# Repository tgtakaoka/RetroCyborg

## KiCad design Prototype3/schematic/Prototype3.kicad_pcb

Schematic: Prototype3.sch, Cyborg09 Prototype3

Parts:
C1, C2, C3, C4, C5: 0.1u; C_0603_1608Metric
C6, C7, C8, C9: 22p; C_0402_1005Metric
J1: Conn_I2C_Master; PinSocket_1x04_P2.54mm_Vertical
J2: Conn_Micro_SD; PinSocket_1x07_P2.54mm_Vertical
J3: Conn_USB_Serial; PinSocket_1x06_P2.54mm_Vertical
J4, J5: Conn_AVR_ISP; PinSocket_1x06_P2.54mm_Vertical
R1, R2: 4k7; R_0603_1608Metric
R3, R4, R5, R6: 10k; R_0603_1608Metric
U1: ATmega1284P-PU; DIP-40_W15.24mm_Socket
U2: HM628128DLP-5; DIP-32_W15.24mm_Socket
U3: HD63C09E; DIP-40_W15.24mm_Socket
U4: ATmega328-PU; DIP-28_W7.62mm_Socket
Y1, Y2: 20MHz; Crystal_SMD_SeikoEpson_FA238-4Pin_3.2x2.5mm

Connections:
/A0: U1.25 (PC3), U2.26 (A9), U3.8 (A0)
/A1: U1.24 (PC2), U2.25 (A11), U3.9 (A1)
/A2: J5.4 (MISO), U2.23 (A10), U3.10 (A2), U4.18 (MISO/PB4)
/A3: J5.5 (MOSI), U2.3 (A14), U3.11 (A3), U4.17 (MOSI/PB3)
/A4: U2.4 (A12), U3.12 (A4), U4.16 (~SS~/PB2)
/A5: U2.5 (A7), U3.13 (A5), U4.2 (RXD/PD0)
/A6: U2.6 (A6), U3.14 (A6), U4.15 (PB1)
/A7: J5.3 (SCK), U2.7 (A5), U3.15 (A7), U4.19 (SCK/PB5)
/A8: U2.8 (A4), U3.16 (A8), U4.14 (PB0)
/A9: U2.9 (A3), U3.17 (A9), U4.3 (TXD/PD1)
/A10: U2.10 (A2), U3.18 (A10), U4.4 (PD2)
/A11: U2.11 (A1), U3.19 (A11), U4.5 (PD3)
/A12: U2.12 (A0), U3.20 (A12), U4.6 (PD4)
/A13: U2.31 (A15), U3.21 (A13), U4.11 (PD5)
/A14: U2.28 (A13), U3.22 (A14), U4.12 (PD6)
/A15: U2.27 (A8), U3.23 (A15), U4.13 (PD7)
/AVMA: U1.26 (PC4), U3.36 (AVMA)
/BA: U1.27 (PC5), U3.6 (BA)
/BS: U1.29 (PC7), U3.5 (BS)
/CLK_E: U2.30 (CS2), U3.34 (E), U4.27 (SDA/PC4)
/CLK_Q: U3.35 (Q), U4.28 (SCL/PC5)
/D0: U1.40 (PA0), U2.21 (Q7), U3.31 (D0)
/D1: U1.39 (PA1), U2.20 (Q6), U3.30 (D1)
/D2: U1.38 (PA2), U2.19 (Q5), U3.29 (D2)
/D3: U1.37 (PA3), U2.18 (Q4), U3.28 (D3)
/D4: U1.36 (PA4), U2.17 (Q3), U3.27 (D4)
/D5: U1.35 (PA5), U2.13 (Q0), U3.26 (D5)
/D6: U1.34 (PA6), U2.14 (Q1), U3.25 (D6)
/D7: U1.33 (PA7), U2.15 (Q2), U3.24 (D7)
/DBG_RX: J3.3 (TXD), U1.14 (RXD0/PD0)
/DBG_TX: J3.2 (RXD), U1.15 (TXD0/PD1)
/LIC: U1.19 (PD5), U3.38 (LIC)
/RD_WR: U1.4 (PB3), U2.29 (WR), U3.32 (R/~W)
/SCL: J1.4 (SCL), R1.2, U1.22 (SCL/PC0)
/SDA: J1.1 (SDA), R2.2, U1.23 (SDA/PC1)
/SD_CD: J2.6 (CD), U1.16 (RXD1/PD2)
/SD_DI: J2.3 (DI), J4.5 (MOSI), U1.6 (MOSI/PB5)
/SD_DO: J2.5 (DO), J4.4 (MISO), U1.7 (MISO/PB6)
/SD_SCK: J2.4 (SCK), J4.3 (SCK), U1.8 (SCK/PB7)
/~ACK: U1.20 (PD6), U4.25 (PC2)
/~DBG_RST~: C5.2, J4.1 (~RESET~), R3.1, U1.9 (~RESET~)
/~DBG_RTS: J3.5 (~CTS), U1.18 (PD4)
/~HALT: U1.1 (PB0), U3.40 (~HALT)
/~INT: U1.17 (TXD1/PD3), U4.26 (PC3)
/~IRQ: U1.2 (PB1), U3.3 (~IRQ)
/~RAM_E: U1.28 (PC6), U2.22 (CS1)
/~RESET: U1.3 (PB2), U3.37 (~RESET)
/~SD_CS: J2.2 (~CS), U1.5 (~SS~/PB4)
/~STEP: U1.21 (PD7), U4.24 (PC1)
GND: C1.2, C2.2, C3.2, C4.2, C6.2, C7.1, C8.2, C9.1, J1.3 (GND), J2.7 (GND), J3.6 (GND), J4.6 (GND), J5.6 (GND), U1.11 (GND), U1.31 (GND), U2.2 (A16), U2.16 (GND), U2.24 (OE), U3.1 (VSS), U3.39 (TSC), U4.8 (GND), U4.22 (GND)
unnamed: C5.1, J3.1 (~DTR)
unnamed: C6.1, U1.13 (XTAL1), Y1.1
unnamed: C7.2, U1.12 (XTAL2), Y1.2
unnamed: C8.1, U4.9 (XTAL1/PB6), Y2.1
unnamed: C9.2, U4.10 (XTAL2/PB7), Y2.2
unnamed: J5.1 (~RESET~), R6.2, U4.1 (PC6/~RESET)
unnamed: R4.1, U3.2 (~NMI)
unnamed: R5.1, U3.4 (~FIRQ)
VCC: C1.1, C2.1, C3.1, C4.1, J1.2 (5V0), J2.1 (VCC), J3.4 (5V0), J4.2 (VCC), J5.2 (VCC), R1.1, R2.1, R3.2, R4.2, R5.2, R6.1, U1.10 (VCC), U1.30 (AVCC), U2.32 (VCC), U3.7 (VCC), U4.7 (VCC), U4.20 (AVCC)

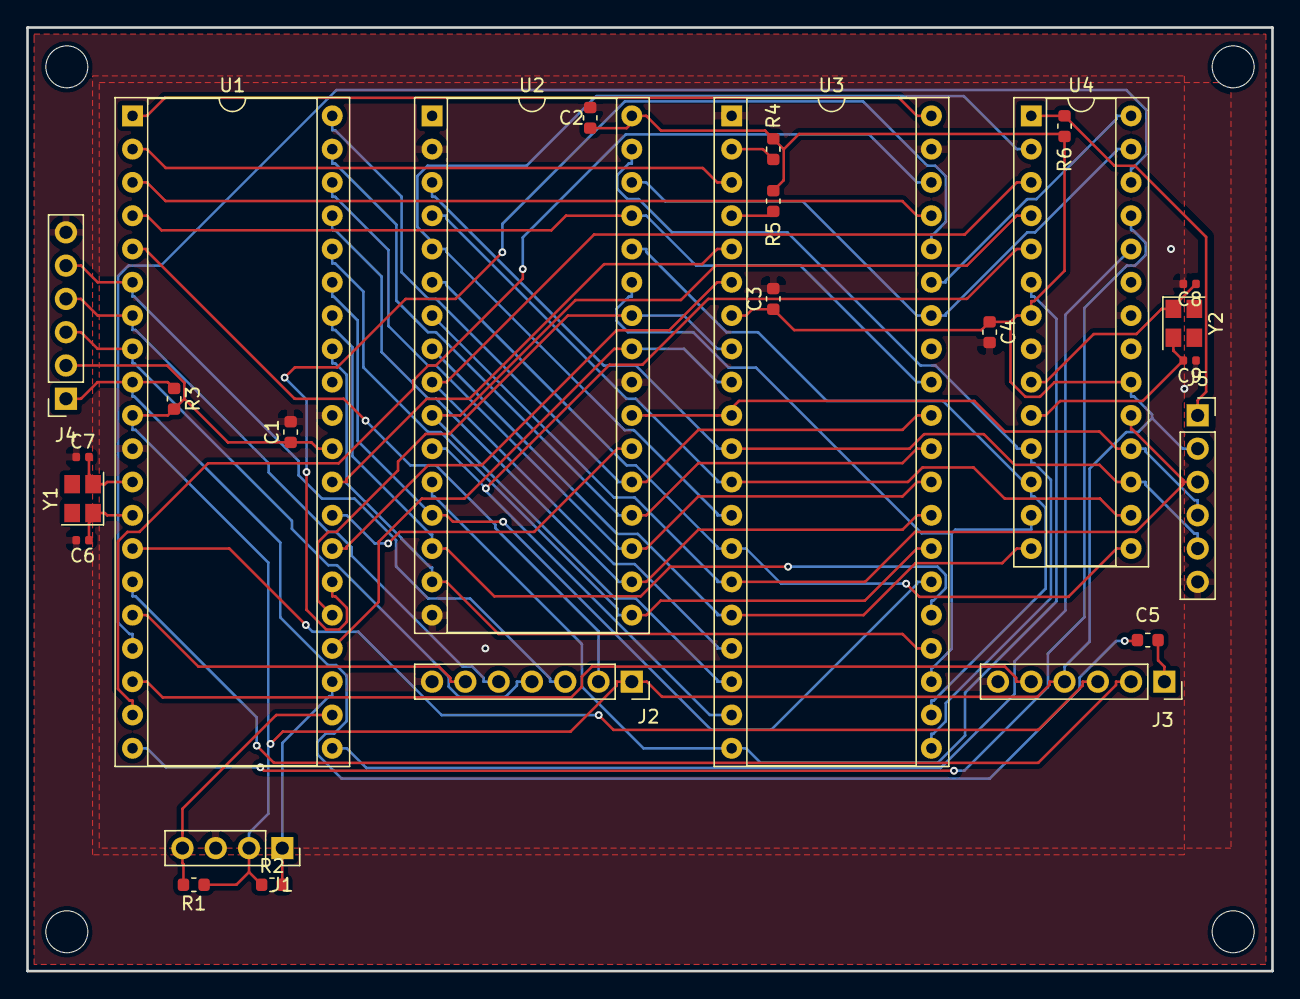
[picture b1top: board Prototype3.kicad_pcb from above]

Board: 2 copper layers, 95.0 x 72.0 mm, 30 parts (0 on the bottom side), 59 nets.

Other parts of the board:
MH1, MH2, MH3, MH4: MountingHole_3.2mm_M3

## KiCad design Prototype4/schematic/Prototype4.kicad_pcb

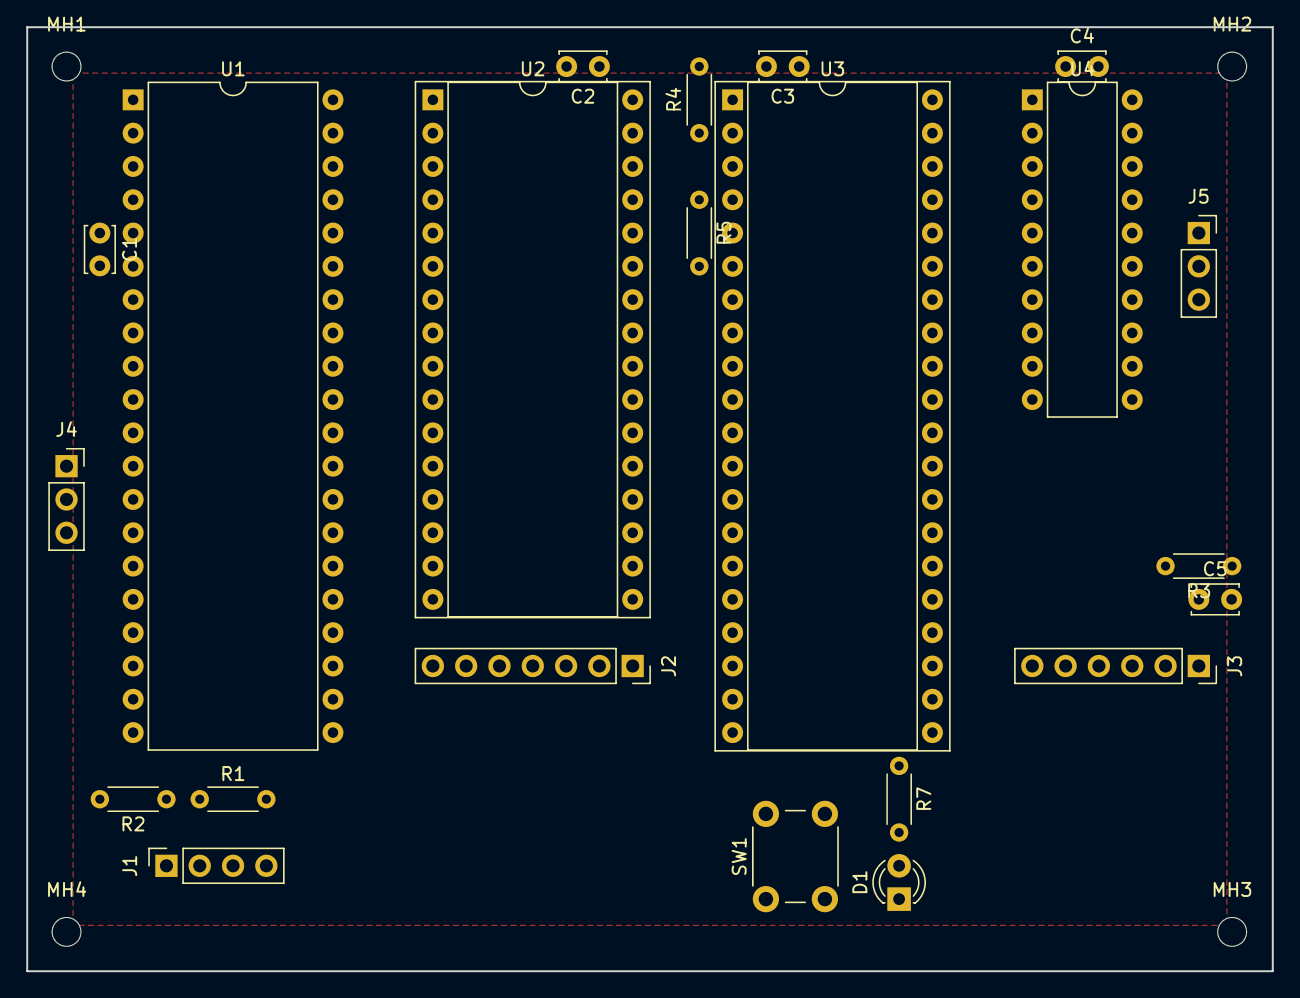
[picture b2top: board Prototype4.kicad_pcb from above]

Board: 2 copper layers, 95.0 x 72.0 mm, 26 parts (0 on the bottom side), 57 nets, no tracks yet.

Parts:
C1, C2, C3, C4, C5: 0.1u; C_Disc_D3.4mm_W2.1mm_P2.50mm
D1: USR_LED; LED_D3.0mm
J1: Conn_I2C_Master; PinSocket_1x04_P2.54mm_Vertical
J2: Conn_Micro_SD; PinSocket_1x07_P2.54mm_Vertical
J3: Conn_USB_Serial; PinSocket_1x06_P2.54mm_Vertical
J4, J5: Conn_AVR_UPDI; PinSocket_1x03_P2.54mm_Vertical
MH1, MH2, MH3, MH4: MountingHole_2.2mm_M2
R1, R2: 4k7; R_Axial_DIN0204_L3.6mm_D1.6mm_P5.08mm_Horizontal
R3, R4, R5: 10k; R_Axial_DIN0204_L3.6mm_D1.6mm_P5.08mm_Horizontal
R7: 560; R_Axial_DIN0204_L3.6mm_D1.6mm_P5.08mm_Horizontal
SW1: USR_SW; SW_PUSH_6mm_H5mm
U1: ATmega4809-P; DIP-40_W15.24mm
U2: HM628128DLP-5; DIP-32_W15.24mm_Socket
U3: HD63C09E; DIP-40_W15.24mm_Socket
U4: ATtiny416-S; DIP-20_W7.62mm

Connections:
/A0: U1.7, U2.26, U3.8
/A1: U1.8, U2.25, U3.9
/A2: U2.23, U3.10
/A3: U2.3, U3.11
/A4: U2.4, U3.12, U4.6
/A5: U2.5, U3.13, U4.2
/A6: U2.6, U3.14, U4.7
/A7: U2.7, U3.15, U4.8
/A8: U2.8, U3.16, U4.9
/A9: U2.9, U3.17, U4.10
/A10: U2.10, U3.18, U4.3
/A11: U2.11, U3.19, U4.4
/A12: U2.12, U3.20, U4.5
/A13: U2.31, U3.21, U4.17
/A14: U2.28, U3.22, U4.18
/A15: U2.27, U3.23, U4.19
/AVMA: U1.26, U3.36
/BA: U1.24, U3.6
/BS: U1.23, U3.5
/CLK_E: U2.30, U3.34, U4.14
/CLK_Q: U3.35, U4.15
/D0: U1.33, U2.21, U3.31
/D1: U1.34, U2.20, U3.30
/D2: U1.35, U2.19, U3.29
/D3: U1.36, U2.18, U3.28
/D4: U1.37, U2.17, U3.27
/D5: U1.38, U2.13, U3.26
/D6: U1.39, U2.14, U3.25
/D7: U1.40, U2.15, U3.24
/DBG_RX: J3.3, U1.1
/DBG_TX: J3.2, U1.2
/LIC: U1.25, U3.38
/RD_WR: U1.27, U2.29, U3.32
/SCL: J1.4, R1.2, U1.4
/SDA: J1.1, R2.2, U1.3
/SD_DI: J2.3, U1.19
/SD_DO: J2.5, U1.20
/SD_SCK: J2.4, U1.21
/~ACK: U1.15, U4.12
/~DBG_RST~: C5.2, R3.1, U1.29
/~HALT: U1.9, U3.40
/~INT: U1.12, U4.13
/~IRQ: U1.10, U3.3
/~RAM_E: U1.28, U2.22
/~RESET: U1.14, U3.37
/~SD_CS: J2.2, U1.22
/~STEP: U1.16, U4.11
/~USR_LED~: D1.1, U1.13
/~USR_SW~: SW1.1, U1.11
GND: C1.2, C2.2, C3.2, C4.2, J1.3, J2.7, J3.5, J3.6, J4.2, J5.2, SW1.2, U1.6, U1.18, U1.32, U2.2, U2.16, U2.24, U3.1, U3.39, U4.20
unnamed: C5.1, J3.1
unnamed: D1.2, R7.2
unnamed: J4.1, U1.30
unnamed: J5.1, U4.16
unnamed: R4.1, U3.2
unnamed: R5.1, U3.4
VCC: C1.1, C2.1, C3.1, C4.1, J1.2, J2.1, J3.4, J4.3, J5.3, R1.1, R2.1, R3.2, R4.2, R5.2, R7.1, U1.5, U1.17, U1.31, U2.32, U3.7, U4.1

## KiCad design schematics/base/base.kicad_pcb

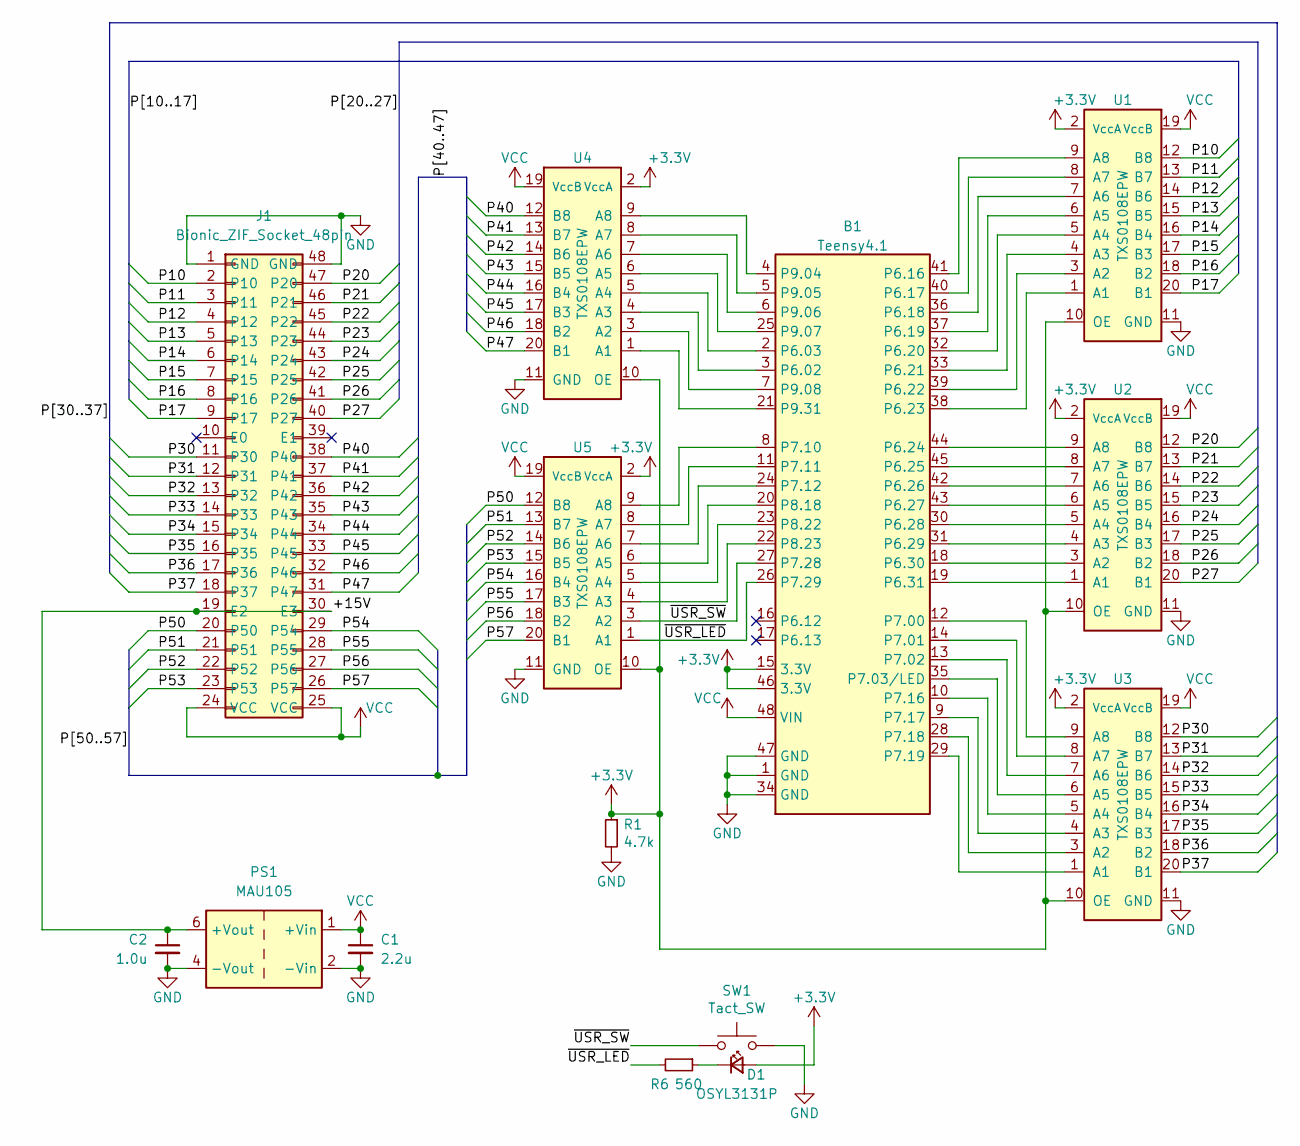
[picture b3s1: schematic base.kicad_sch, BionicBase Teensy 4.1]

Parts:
B1: Teensy4.1; DIP-48_W15.24mm
C1: 2.2u; C_0603_1608Metric_Pad1.08x0.95mm_HandSolder
C2: 1.0u; C_0603_1608Metric_Pad1.08x0.95mm_HandSolder
D1: OSYL3131P; LED_D3.0mm
J1: Bionic_ZIF_Socket_48pin; Aries_ZIF_socket_DIP-48-pin
PS1: MAU105; Converter_DCDC_Minmax_MAU100_THT
R1: 4.7k; R_Axial_DIN0204_L3.6mm_D1.6mm_P5.08mm_Horizontal
R6: 560; R_Axial_DIN0204_L3.6mm_D1.6mm_P5.08mm_Horizontal
SW1: Tact_SW; Tact_SW_6x6mm
U1, U2, U3, U4, U5: TXS0108EPW; TSSOP-20_4.4x6.5mm_P0.65mm

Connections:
+3.3V: B1.15 (3.3V), B1.46 (3.3V), D1.2 (A), R1.1, U1.2 (VccA), U1.10 (OE), U2.2 (VccA), U2.10 (OE), U3.2 (VccA), U3.10 (OE), U4.2 (VccA), U4.10 (OE), U5.2 (VccA), U5.10 (OE)
/+15V: C2.1, J1.19 (E2), J1.30 (E3), PS1.6 (+Vout)
/P10: J1.2 (P10), U1.12 (B8)
/P11: J1.3 (P11), U1.13 (B7)
/P12: J1.4 (P12), U1.14 (B6)
/P13: J1.5 (P13), U1.15 (B5)
/P14: J1.6 (P14), U1.16 (B4)
/P15: J1.7 (P15), U1.17 (B3)
/P16: J1.8 (P16), U1.18 (B2)
/P17: J1.9 (P17), U1.20 (B1)
/P20: J1.47 (P20), U2.12 (B8)
/P21: J1.46 (P21), U2.13 (B7)
/P22: J1.45 (P22), U2.14 (B6)
/P23: J1.44 (P23), U2.15 (B5)
/P24: J1.43 (P24), U2.16 (B4)
/P25: J1.42 (P25), U2.17 (B3)
/P26: J1.41 (P26), U2.18 (B2)
/P27: J1.40 (P27), U2.20 (B1)
/P30: J1.11 (P30), U3.12 (B8)
/P31: J1.12 (P31), U3.13 (B7)
/P32: J1.13 (P32), U3.14 (B6)
/P33: J1.14 (P33), U3.15 (B5)
/P34: J1.15 (P34), U3.16 (B4)
/P35: J1.16 (P35), U3.17 (B3)
/P36: J1.17 (P36), U3.18 (B2)
/P37: J1.18 (P37), U3.20 (B1)
/P40: J1.38 (P40), U4.12 (B8)
/P41: J1.37 (P41), U4.13 (B7)
/P42: J1.36 (P42), U4.14 (B6)
/P43: J1.35 (P43), U4.15 (B5)
/P44: J1.34 (P44), U4.16 (B4)
/P45: J1.33 (P45), U4.17 (B3)
/P46: J1.32 (P46), U4.18 (B2)
/P47: J1.31 (P47), U4.20 (B1)
/P50: J1.20 (P50), U5.12 (B8)
/P51: J1.21 (P51), U5.13 (B7)
/P52: J1.22 (P52), U5.14 (B6)
/P53: J1.23 (P53), U5.15 (B5)
/P54: J1.29 (P54), U5.16 (B4)
/P55: J1.28 (P55), U5.17 (B3)
/P56: J1.27 (P56), U5.18 (B2)
/P57: J1.26 (P57), U5.20 (B1)
/~USR_LED: B1.26 (P7.29), R6.2, U5.1 (A1)
/~USR_SW: B1.27 (P7.28), SW1.1, U5.3 (A2)
GND: B1.1 (GND), B1.34 (GND), B1.47 (GND), C1.2, C2.2, J1.1 (GND), J1.48 (GND), PS1.2 (-Vin), PS1.4 (-Vout), R1.2, SW1.2, U1.11 (GND), U2.11 (GND), U3.11 (GND), U4.11 (GND), U5.11 (GND)
unnamed: B1.3 (P6.02), U4.4 (A3)
unnamed: B1.2 (P6.03), U4.5 (A4)
unnamed: B1.41 (P6.16), U1.9 (A8)
unnamed: B1.40 (P6.17), U1.8 (A7)
unnamed: B1.36 (P6.18), U1.7 (A6)
unnamed: B1.37 (P6.19), U1.6 (A5)
unnamed: B1.32 (P6.20), U1.5 (A4)
unnamed: B1.33 (P6.21), U1.4 (A3)
unnamed: B1.39 (P6.22), U1.3 (A2)
unnamed: B1.38 (P6.23), U1.1 (A1)
unnamed: B1.44 (P6.24), U2.9 (A8)
unnamed: B1.45 (P6.25), U2.8 (A7)
unnamed: B1.42 (P6.26), U2.7 (A6)
unnamed: B1.43 (P6.27), U2.6 (A5)
unnamed: B1.30 (P6.28), U2.5 (A4)
unnamed: B1.31 (P6.29), U2.4 (A3)
unnamed: B1.18 (P6.30), U2.3 (A2)
unnamed: B1.19 (P6.31), U2.1 (A1)
unnamed: B1.12 (P7.00), U3.9 (A8)
unnamed: B1.14 (P7.01), U3.8 (A7)
unnamed: B1.13 (P7.02), U3.7 (A6)
unnamed: B1.35 (P7.03/LED), U3.6 (A5)
unnamed: B1.8 (P7.10), U5.9 (A8)
unnamed: B1.11 (P7.11), U5.8 (A7)
unnamed: B1.24 (P7.12), U5.7 (A6)
unnamed: B1.10 (P7.16), U3.5 (A4)
unnamed: B1.9 (P7.17), U3.4 (A3)
unnamed: B1.28 (P7.18), U3.3 (A2)
unnamed: B1.29 (P7.19), U3.1 (A1)
unnamed: B1.20 (P8.18), U5.6 (A5)
unnamed: B1.23 (P8.22), U5.5 (A4)
unnamed: B1.22 (P8.23), U5.4 (A3)
unnamed: B1.4 (P9.04), U4.9 (A8)
unnamed: B1.5 (P9.05), U4.8 (A7)
unnamed: B1.6 (P9.06), U4.7 (A6)
unnamed: B1.25 (P9.07), U4.6 (A5)
unnamed: B1.7 (P9.08), U4.3 (A2)
unnamed: B1.21 (P9.31), U4.1 (A1)
unnamed: D1.1 (K), R6.1
VCC: B1.48 (VIN), C1.1, J1.24 (VCC), J1.25 (VCC), PS1.1 (+Vin), U1.19 (VccB), U2.19 (VccB), U3.19 (VccB), U4.19 (VccB), U5.19 (VccB)

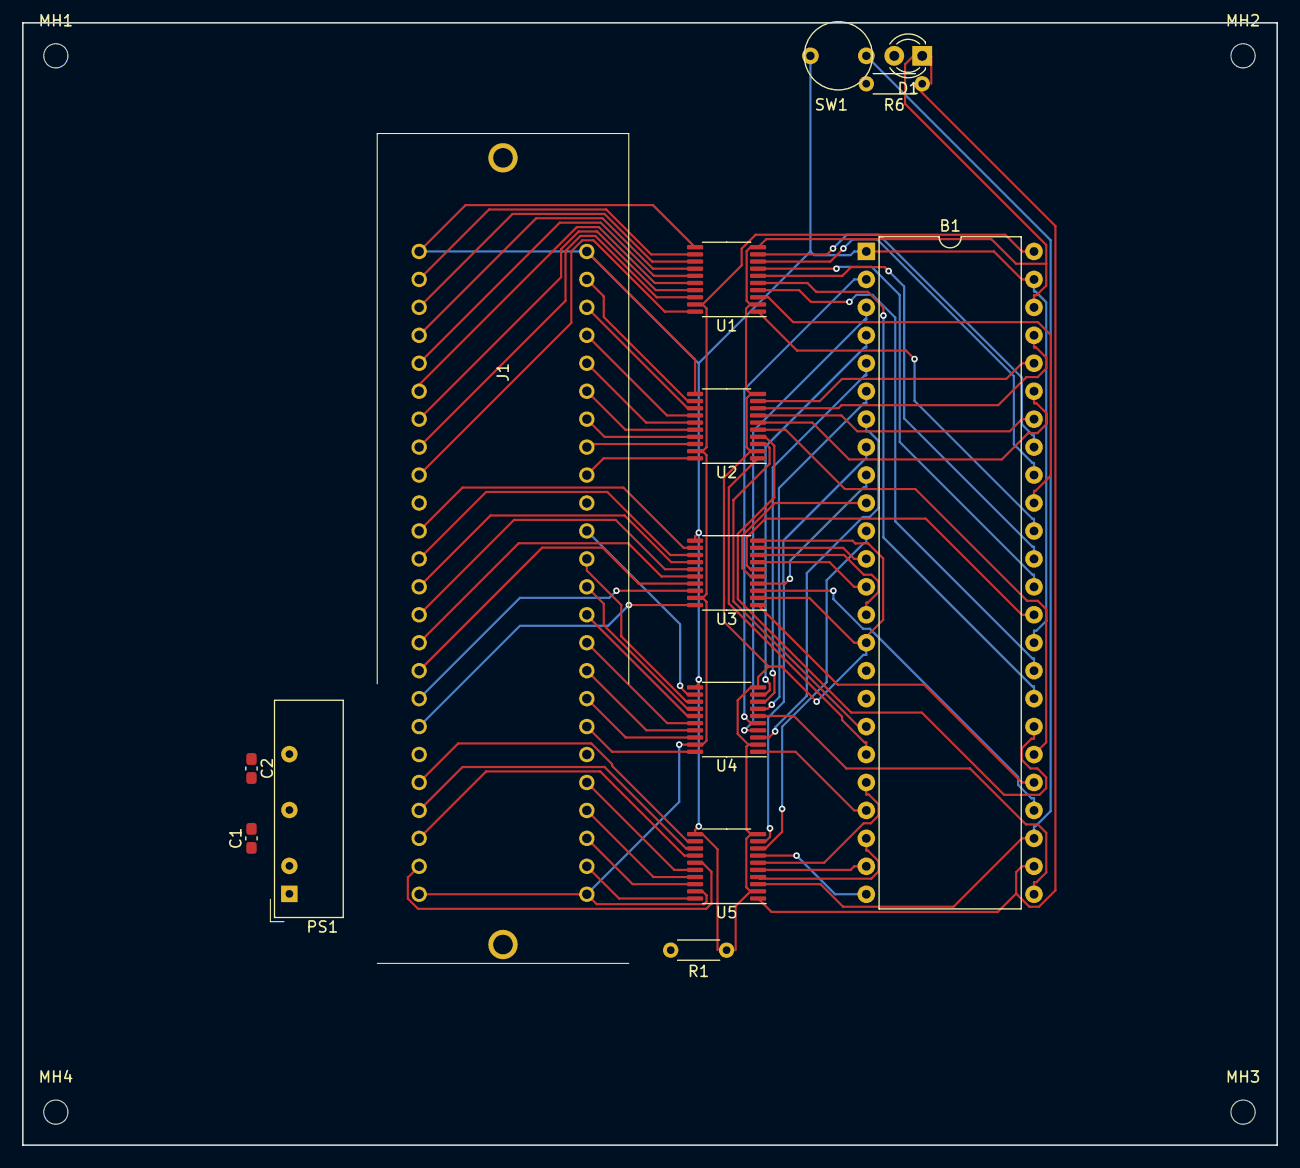
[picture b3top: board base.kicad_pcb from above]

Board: 2 copper layers, 114.0 x 102.0 mm, 18 parts (0 on the bottom side), 85 nets.

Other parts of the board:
MH1, MH2, MH3, MH4: MountingHole_2.2mm_M2

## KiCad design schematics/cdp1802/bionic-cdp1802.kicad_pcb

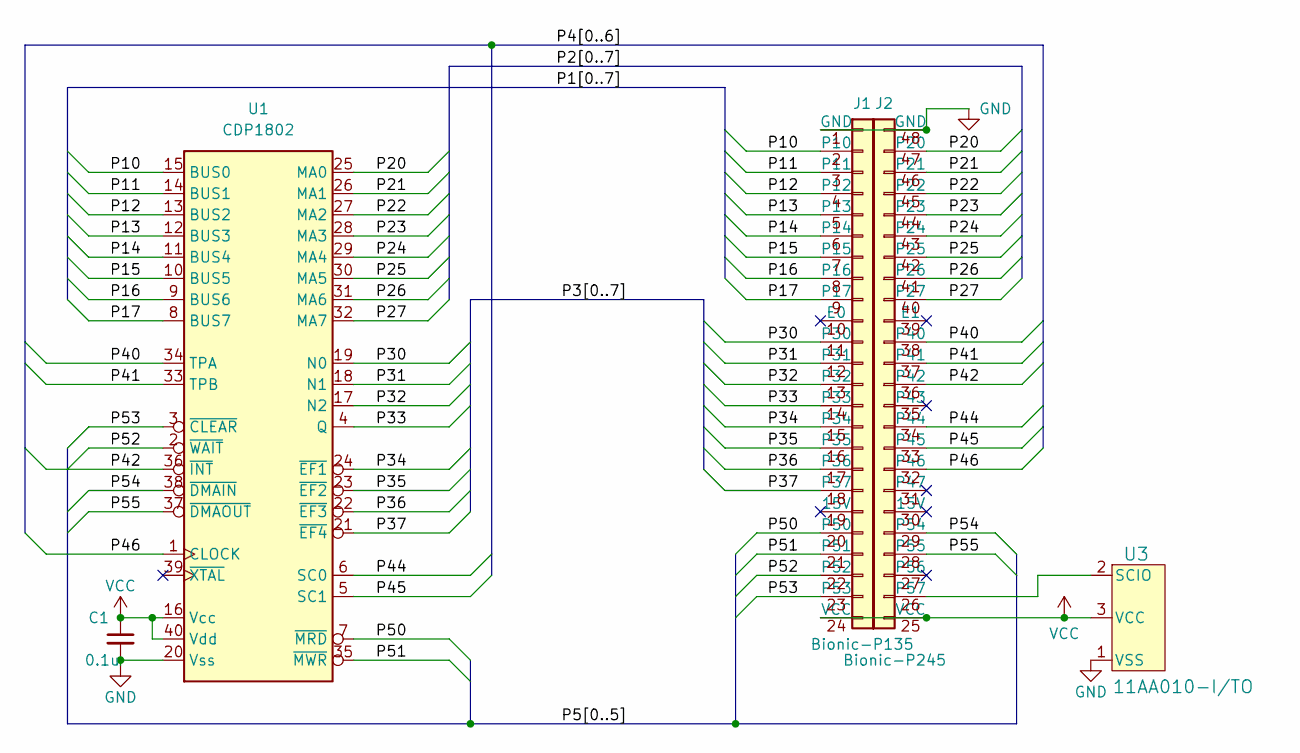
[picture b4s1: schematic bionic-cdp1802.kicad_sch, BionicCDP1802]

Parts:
C1: 0.1u; C_Disc_D3.4mm_W2.1mm_P2.50mm
J1: Bionic-P135; Bionic-P135_Vertical
J2: Bionic-P245; Bionic-P245_Vertical
U1: CDP1802; DIP-40_W15.24mm
U3: 11AA010-I/TO; TO-92_MC_MCH

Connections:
/P10: J1.2 (P10), U1.15 (BUS0)
/P11: J1.3 (P11), U1.14 (BUS1)
/P12: J1.4 (P12), U1.13 (BUS2)
/P13: J1.5 (P13), U1.12 (BUS3)
/P14: J1.6 (P14), U1.11 (BUS4)
/P15: J1.7 (P15), U1.10 (BUS5)
/P16: J1.8 (P16), U1.9 (BUS6)
/P17: J1.9 (P17), U1.8 (BUS7)
/P20: J2.47 (P20), U1.25 (MA0)
/P21: J2.46 (P21), U1.26 (MA1)
/P22: J2.45 (P22), U1.27 (MA2)
/P23: J2.44 (P23), U1.28 (MA3)
/P24: J2.43 (P24), U1.29 (MA4)
/P25: J2.42 (P25), U1.30 (MA5)
/P26: J2.41 (P26), U1.31 (MA6)
/P27: J2.40 (P27), U1.32 (MA7)
/P30: J1.11 (P30), U1.19 (N0)
/P31: J1.12 (P31), U1.18 (N1)
/P32: J1.13 (P32), U1.17 (N2)
/P33: J1.14 (P33), U1.4 (Q)
/P34: J1.15 (P34), U1.24 (~EF1)
/P35: J1.16 (P35), U1.23 (~EF2)
/P36: J1.17 (P36), U1.22 (~EF3)
/P37: J1.18 (P37), U1.21 (~EF4)
/P40: J2.38 (P40), U1.34 (TPA)
/P41: J2.37 (P41), U1.33 (TPB)
/P42: J2.36 (P42), U1.36 (~INT)
/P44: J2.34 (P44), U1.6 (SC0)
/P45: J2.33 (P45), U1.5 (SC1)
/P46: J2.32 (P46), U1.1 (CLOCK)
/P50: J1.20 (P50), U1.7 (~MRD)
/P51: J1.21 (P51), U1.35 (~MWR)
/P52: J1.22 (P52), U1.2 (~WAIT)
/P53: J1.23 (P53), U1.3 (~CLEAR)
/P54: J2.29 (P54), U1.38 (~DMAIN)
/P55: J2.28 (P55), U1.37 (~DMAOUT)
GND: C1.2, J1.1 (GND), J2.48 (GND), U1.20 (Vss), U3.1 (VSS)
unnamed: J2.26 (P57), U3.2 (SCIO)
VCC: C1.1, J1.24 (VCC), J2.25 (VCC), U1.16 (Vcc), U1.40 (Vdd), U3.3 (VCC)

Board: 2 copper layers, 9 parts (0 on the bottom side), 39 nets, no tracks yet.

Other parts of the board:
MH1, MH2, MH3, MH4: MountingHole_3.2mm_M3

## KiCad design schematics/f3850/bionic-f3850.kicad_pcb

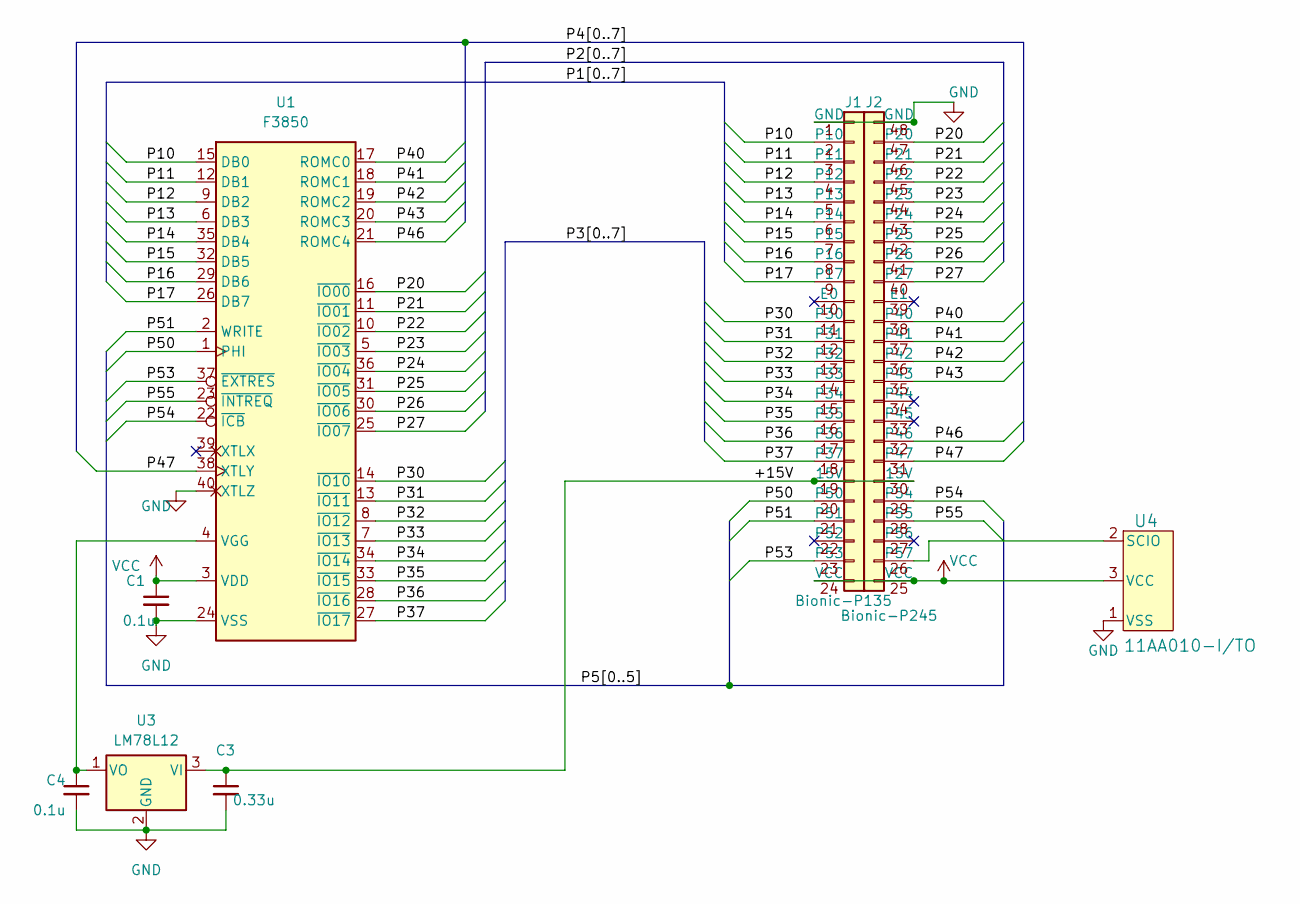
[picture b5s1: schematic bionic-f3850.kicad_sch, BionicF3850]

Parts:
C1, C4: 0.1u; C_Disc_D3.4mm_W2.1mm_P2.50mm
C3: 0.33u; C_Disc_D3.4mm_W2.1mm_P2.50mm
J1: Bionic-P135; Bionic-P135_Vertical
J2: Bionic-P245; Bionic-P245_Vertical
U1: F3850; DIP-40_W15.24mm
U3: LM78L12; TO-92_Inline
U4: 11AA010-I/TO; TO-92_MC_MCH

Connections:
/+15V: C3.1, J1.19 (15V), J2.30 (15V), U3.3 (VI)
/P10: J1.2 (P10), U1.15 (DB0)
/P11: J1.3 (P11), U1.12 (DB1)
/P12: J1.4 (P12), U1.9 (DB2)
/P13: J1.5 (P13), U1.6 (DB3)
/P14: J1.6 (P14), U1.35 (DB4)
/P15: J1.7 (P15), U1.32 (DB5)
/P16: J1.8 (P16), U1.29 (DB6)
/P17: J1.9 (P17), U1.26 (DB7)
/P20: J2.47 (P20), U1.16 (~IO00)
/P21: J2.46 (P21), U1.11 (~IO01)
/P22: J2.45 (P22), U1.10 (~IO02)
/P23: J2.44 (P23), U1.5 (~IO03)
/P24: J2.43 (P24), U1.36 (~IO04)
/P25: J2.42 (P25), U1.31 (~IO05)
/P26: J2.41 (P26), U1.30 (~IO06)
/P27: J2.40 (P27), U1.25 (~IO07)
/P30: J1.11 (P30), U1.14 (~IO10)
/P31: J1.12 (P31), U1.13 (~IO11)
/P32: J1.13 (P32), U1.8 (~IO12)
/P33: J1.14 (P33), U1.7 (~IO13)
/P34: J1.15 (P34), U1.34 (~IO14)
/P35: J1.16 (P35), U1.33 (~IO15)
/P36: J1.17 (P36), U1.28 (~IO16)
/P37: J1.18 (P37), U1.27 (~IO17)
/P40: J2.38 (P40), U1.17 (ROMC0)
/P41: J2.37 (P41), U1.18 (ROMC1)
/P42: J2.36 (P42), U1.19 (ROMC2)
/P43: J2.35 (P43), U1.20 (ROMC3)
/P46: J2.32 (P46), U1.21 (ROMC4)
/P47: J2.31 (P47), U1.38 (XTLY)
/P50: J1.20 (P50), U1.1 (PHI)
/P51: J1.21 (P51), U1.2 (WRITE)
/P53: J1.23 (P53), U1.37 (~EXTRES)
/P54: J2.29 (P54), U1.22 (~ICB)
/P55: J2.28 (P55), U1.23 (~INTREQ)
GND: C1.2, C3.2, C4.2, J1.1 (GND), J2.48 (GND), U1.24 (VSS), U1.40 (XTLZ), U3.2 (GND), U4.1 (VSS)
unnamed: J2.26 (P57), U4.2 (SCIO)
unnamed: C4.1, U1.4 (VGG), U3.1 (VO)
VCC: C1.1, J1.24 (VCC), J2.25 (VCC), U1.3 (VDD), U4.3 (VCC)

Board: 2 copper layers, 12 parts (0 on the bottom side), 40 nets, no tracks yet.

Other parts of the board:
MH1, MH2, MH3, MH4: MountingHole_3.2mm_M3

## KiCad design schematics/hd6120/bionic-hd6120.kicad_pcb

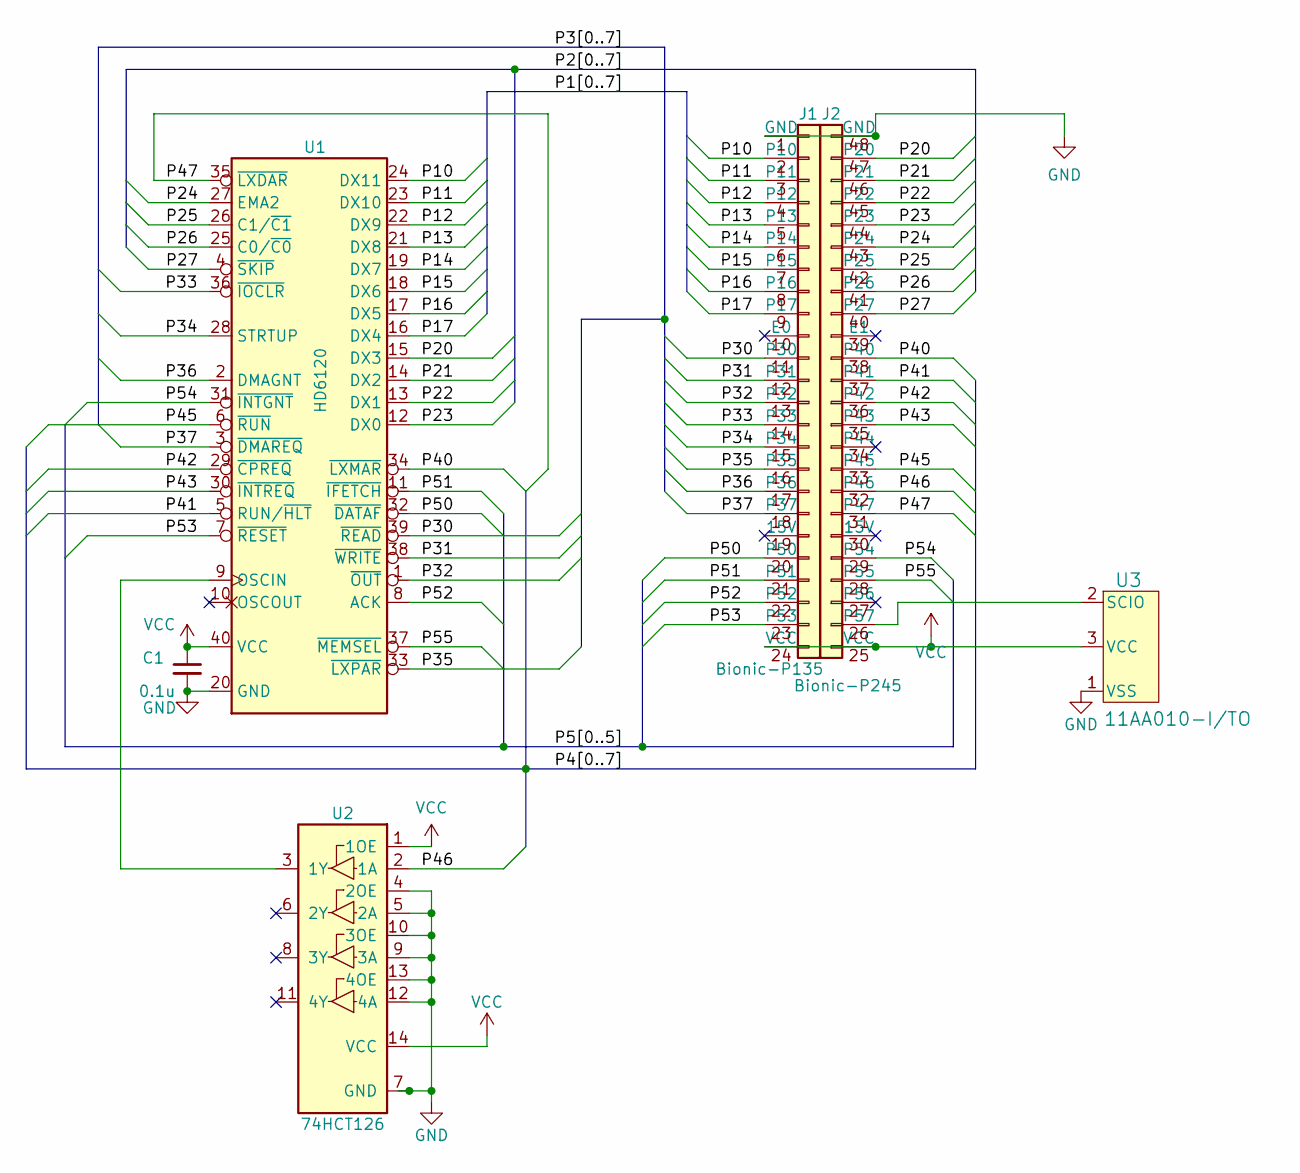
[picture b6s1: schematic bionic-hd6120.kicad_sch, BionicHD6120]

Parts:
C1: 0.1u; C_Disc_D3.4mm_W2.1mm_P2.50mm
J1: Bionic-P135; Bionic-P135_Vertical
J2: Bionic-P245; Bionic-P245_Vertical
U1: HD6120; DIP-40_W15.24mm
U2: 74HCT126; DIP-14_W7.62mm
U3: 11AA010-I/TO; TO-92_MC_MCH

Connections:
/P10: J1.2 (P10), U1.24 (DX11)
/P11: J1.3 (P11), U1.23 (DX10)
/P12: J1.4 (P12), U1.22 (DX9)
/P13: J1.5 (P13), U1.21 (DX8)
/P14: J1.6 (P14), U1.19 (DX7)
/P15: J1.7 (P15), U1.18 (DX6)
/P16: J1.8 (P16), U1.17 (DX5)
/P17: J1.9 (P17), U1.16 (DX4)
/P20: J2.47 (P20), U1.15 (DX3)
/P21: J2.46 (P21), U1.14 (DX2)
/P22: J2.45 (P22), U1.13 (DX1)
/P23: J2.44 (P23), U1.12 (DX0)
/P24: J2.43 (P24), U1.27 (EMA2)
/P25: J2.42 (P25), U1.26 (C1/~C1)
/P26: J2.41 (P26), U1.25 (C0/~C0)
/P27: J2.40 (P27), U1.4 (~SKIP)
/P30: J1.11 (P30), U1.39 (~READ)
/P31: J1.12 (P31), U1.38 (~WRITE)
/P32: J1.13 (P32), U1.1 (~OUT)
/P33: J1.14 (P33), U1.36 (~IOCLR)
/P34: J1.15 (P34), U1.28 (STRTUP)
/P35: J1.16 (P35), U1.33 (~LXPAR)
/P36: J1.17 (P36), U1.2 (DMAGNT)
/P37: J1.18 (P37), U1.3 (~DMAREQ)
/P40: J2.38 (P40), U1.34 (~LXMAR)
/P41: J2.37 (P41), U1.5 (RUN/~HLT)
/P42: J2.36 (P42), U1.29 (~CPREQ)
/P43: J2.35 (P43), U1.30 (~INTREQ)
/P45: J2.33 (P45), U1.6 (~RUN)
/P46: J2.32 (P46), U2.2 (1A)
/P47: J2.31 (P47), U1.35 (~LXDAR)
/P50: J1.20 (P50), U1.32 (~DATAF)
/P51: J1.21 (P51), U1.11 (~IFETCH)
/P52: J1.22 (P52), U1.8 (ACK)
/P53: J1.23 (P53), U1.7 (~RESET)
/P54: J2.29 (P54), U1.31 (~INTGNT)
/P55: J2.28 (P55), U1.37 (~MEMSEL)
GND: C1.2, J1.1 (GND), J2.48 (GND), U1.20 (GND), U2.4 (2OE), U2.5 (2A), U2.7 (GND), U2.9 (3A), U2.10 (3OE), U2.12 (4A), U2.13 (4OE), U3.1 (VSS)
unnamed: J2.26 (P57), U3.2 (SCIO)
unnamed: U1.9 (OSCIN), U2.3 (1Y)
VCC: C1.1, J1.24 (VCC), J2.25 (VCC), U1.40 (VCC), U2.1 (1OE), U2.14 (VCC), U3.3 (VCC)

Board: 2 copper layers, 10 parts (0 on the bottom side), 41 nets, no tracks yet.

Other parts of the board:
MH1, MH2, MH3, MH4: MountingHole_3.2mm_M3
